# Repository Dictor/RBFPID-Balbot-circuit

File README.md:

# circuit of RBF-PID Balancing Robot 
- [schemetic](./circuit.pdf)
- [pcb](./pcb.pdf)
- [STM32 configuration](./stm32ioc.pdf)

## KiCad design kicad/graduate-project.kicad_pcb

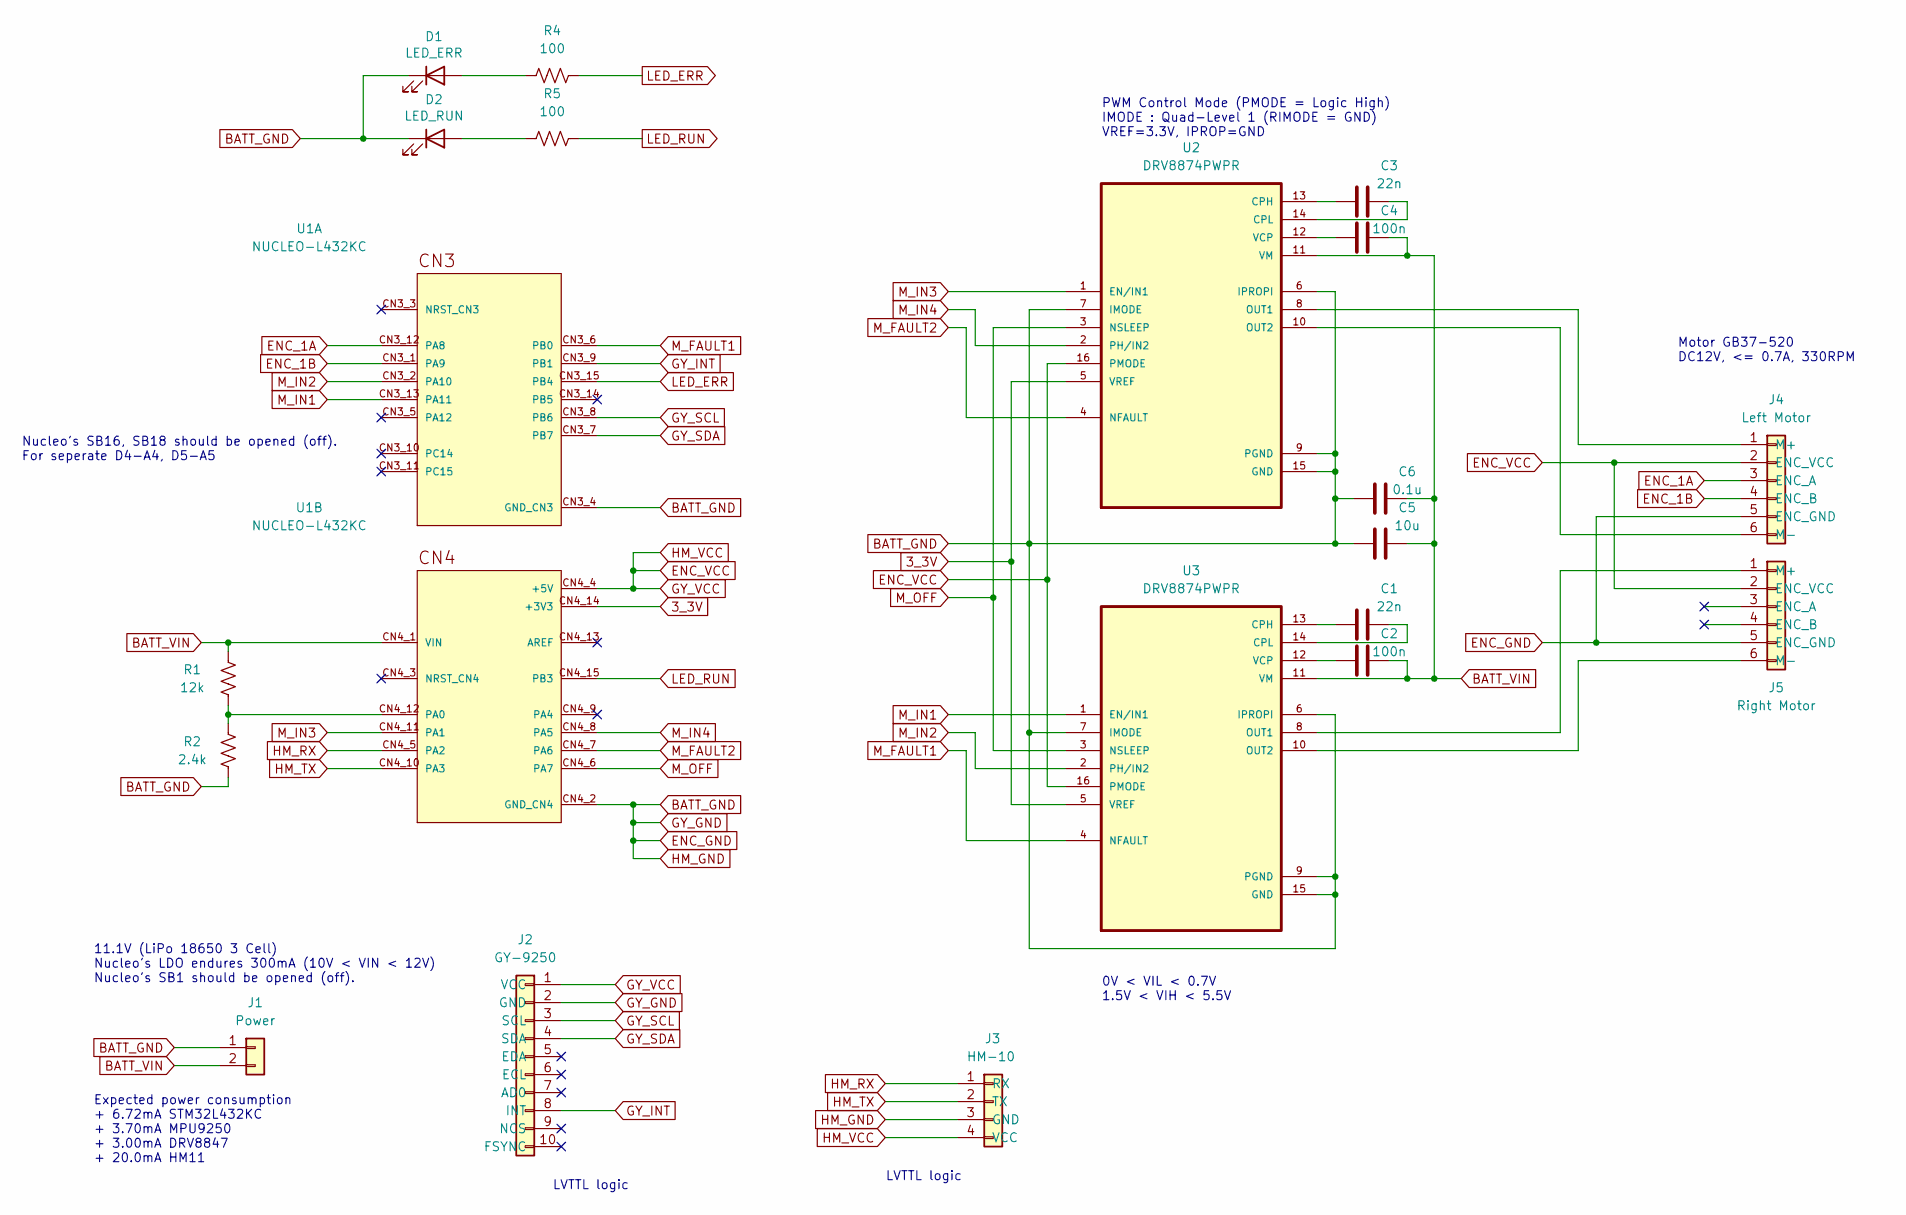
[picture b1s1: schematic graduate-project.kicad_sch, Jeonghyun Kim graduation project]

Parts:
C1, C3: 22n; C_0603_1608Metric
C2, C4: 100n; C_0603_1608Metric
C5: 10u; C_0603_1608Metric
C6: 0.1u; C_0603_1608Metric
D1: LED_ERR; LED_D3.0mm
D2: LED_RUN; LED_D3.0mm
J1: Power; AMASS_XT30U-F_1x02_P5.0mm_Vertical
J2: GY-9250; PinSocket_1x10_P2.54mm_Vertical
J3: HM-10; PinSocket_1x04_P2.54mm_Vertical
J4: Left Motor; PinSocket_1x06_P2.54mm_Vertical
J5: Right Motor; PinSocket_1x06_P2.54mm_Vertical
R1: 12k; R_0603_1608Metric
R2: 2.4k; R_0603_1608Metric
R4, R5: 100; R_0603_1608Metric
U1: NUCLEO-L432KC; MODULE_NUCLEO-L432KC; PARTREV N/A
U2, U3: DRV8874PWPR; SOP65P640X120-17N

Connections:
3_3V: U1.CN4_14 (+3V3), U2.5 (VREF), U3.5 (VREF)
BATT_GND: C5.1, C6.1, D1.1 (K), D2.1 (K), J1.1, J2.2 (GND), J3.3 (GND), J4.5 (ENC_GND), J5.5 (ENC_GND), R2.1, U1.CN3_4 (GND_CN3), U1.CN4_2 (GND_CN4), U2.6 (IPROPI), U2.7 (IMODE), U2.9 (PGND), U2.15 (GND), U2.17, U3.6 (IPROPI), U3.7 (IMODE), U3.9 (PGND), U3.15 (GND), U3.17
BATT_VIN: C2.2, C4.2, C5.2, C6.2, J1.2, R1.2, U1.CN4_1 (VIN), U2.11 (VM), U3.11 (VM)
ENC_1A: J4.3 (ENC_A), U1.CN3_12 (PA8)
ENC_1B: J4.4 (ENC_B), U1.CN3_1 (PA9)
ENC_VCC: J2.1 (VCC), J3.4 (VCC), J4.2 (ENC_VCC), J5.2 (ENC_VCC), U1.CN4_4 (+5V), U2.16 (PMODE), U3.16 (PMODE)
GY_INT: J2.8 (INT), U1.CN3_9 (PB1)
GY_SCL: J2.3 (SCL), U1.CN3_8 (PB6)
GY_SDA: J2.4 (SDA), U1.CN3_7 (PB7)
HM_RX: J3.1 (RX), U1.CN4_5 (PA2)
HM_TX: J3.2 (TX), U1.CN4_10 (PA3)
LED_ERR: R4.2, U1.CN3_15 (PB4)
LED_RUN: R5.2, U1.CN4_15 (PB3)
M_FAULT1: U1.CN3_6 (PB0), U3.4 (NFAULT)
M_FAULT2: U1.CN4_7 (PA6), U2.4 (NFAULT)
M_IN1: U1.CN3_13 (PA11), U3.1 (EN/IN1)
M_IN2: U1.CN3_2 (PA10), U3.2 (PH/IN2)
M_IN3: U1.CN4_11 (PA1), U2.1 (EN/IN1)
M_IN4: U1.CN4_8 (PA5), U2.2 (PH/IN2)
M_OFF: U1.CN4_6 (PA7), U2.3 (NSLEEP), U3.3 (NSLEEP)
unnamed: C1.1, U3.13 (CPH)
unnamed: C1.2, U3.14 (CPL)
unnamed: C2.1, U3.12 (VCP)
unnamed: C3.1, U2.13 (CPH)
unnamed: C3.2, U2.14 (CPL)
unnamed: C4.1, U2.12 (VCP)
unnamed: D1.2 (A), R4.1
unnamed: D2.2 (A), R5.1
unnamed: J5.1 (M+), U3.8 (OUT1)
unnamed: J5.6 (M-), U3.10 (OUT2)
unnamed: R1.1, R2.2, U1.CN4_12 (PA0)
unnamed: J4.1 (M+), U2.8 (OUT1)
unnamed: J4.6 (M-), U2.10 (OUT2)

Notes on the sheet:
11.1V (LiPo 18650 3 Cell) Nucleo's LDO endures 300mA (10V < VIN < 12V) Nucleo's SB1 should be opened (off).
PWM Control Mode (PMODE = Logic High) IMODE : Quad-Level 1 (RIMODE = GND) VREF=3.3V, IPROP=GND
LVTTL logic
Motor GB37-520 DC12V, <= 0.7A, 330RPM
Expected power consumption + 6.72mA STM32L432KC + 3.70mA MPU9250 + 3.00mA DRV8847 + 20.0mA HM11
0V < VIL < 0.7V 1.5V < VIH < 5.5V
Nucleo's SB16, SB18 should be opened (off). For seperate D4-A4, D5-A5

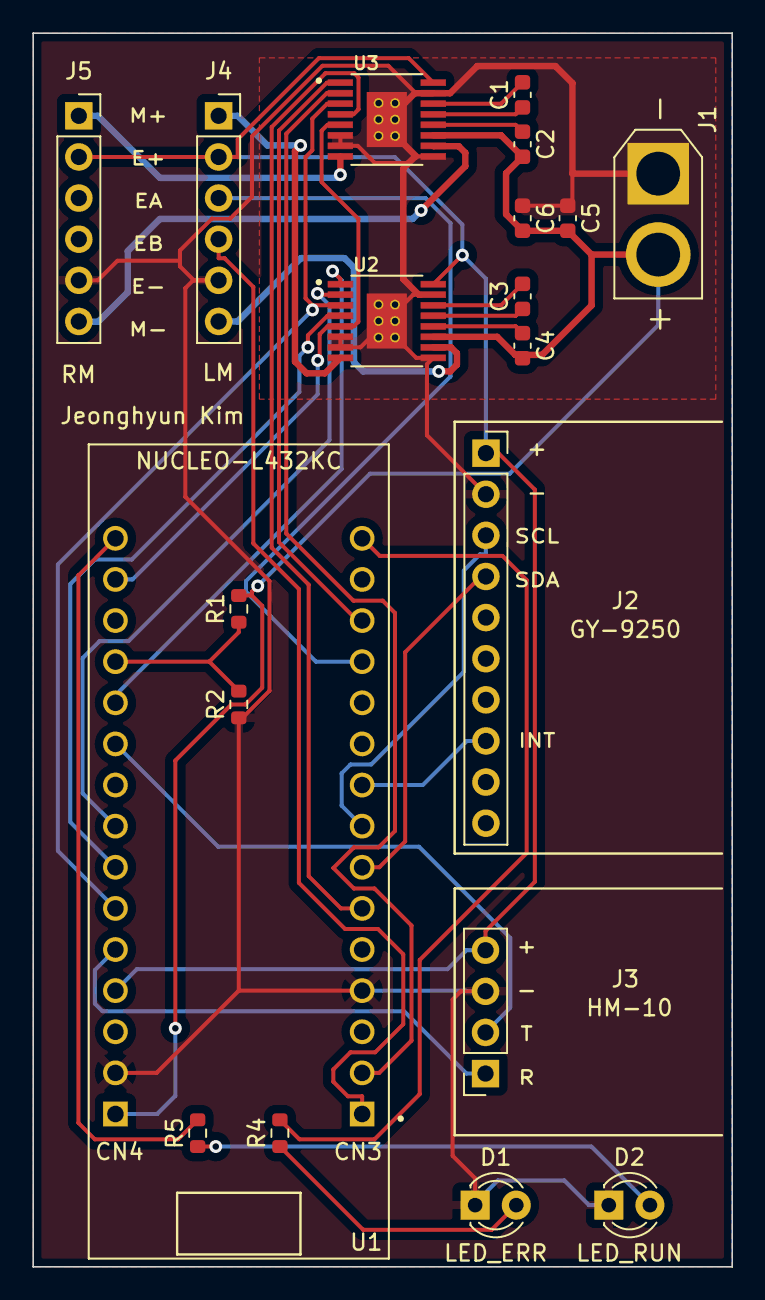
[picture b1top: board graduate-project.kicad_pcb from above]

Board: 2 copper layers, 43.2 x 76.2 mm, 20 parts (0 on the bottom side), 33 nets.

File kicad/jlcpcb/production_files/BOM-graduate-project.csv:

Comment,Designator,Footprint,LCSC
100n,"C2,C4",C_0603_1608Metric,C1591
DRV8874PWPR,"U2,U3",SOP65P640X120-17N,C1855818
22n,"C1,C3",C_0603_1608Metric,C21122
100,"R4,R5",R_0603_1608Metric,C22775
12k,R1,R_0603_1608Metric,C22790
2.4k,R2,R_0603_1608Metric,C465465
10u,C5,C_0603_1608Metric,C70225
0.1u,C6,C_0603_1608Metric,C710755
Power,J1,AMASS_XT30U-F_1x02_P5.0mm_Vertical,C99101

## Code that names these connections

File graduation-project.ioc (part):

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Mcu.Name=STM32L432K(B-C)Ux
Mcu.Package=UFQFPN32
Mcu.UserName=STM32L432KCUx
PA0.Signal=ADCx_IN5
PA1.GPIOParameters=GPIO_Label
PA1.GPIO_Label=M_IN3
PA1.Signal=S_TIM2_CH2
PA10.GPIOParameters=GPIO_Label
PA10.GPIO_Label=M_IN2
PA10.Signal=S_TIM1_CH3
PA11.GPIOParameters=GPIO_Label
PA11.GPIO_Label=M_IN1
PA11.Signal=S_TIM1_CH4
PA13\ (JTMS-SWDIO).GPIOParameters=GPIO_Label
PA13\ (JTMS-SWDIO).GPIO_Label=SWDIO
PA13\ (JTMS-SWDIO).Mode=Serial_Wire
PA13\ (JTMS-SWDIO).Signal=SYS_JTMS-SWDIO
PA14\ (JTCK-SWCLK).GPIOParameters=GPIO_Label
PA14\ (JTCK-SWCLK).GPIO_Label=SWCLK
PA14\ (JTCK-SWCLK).Mode=Serial_Wire
PA14\ (JTCK-SWCLK).Signal=SYS_JTCK-SWCLK
PA2.GPIOParameters=GPIO_Label
PA2.GPIO_Label=VCP_TX
PA2.Mode=Asynchronous
PA2.Signal=USART2_TX
PA3.GPIOParameters=GPIO_Label
PA3.GPIO_Label=VCP_RX
PA3.Mode=Asynchronous
PA3.Signal=USART2_RX
PA5.GPIOParameters=GPIO_Label
PA5.GPIO_Label=M_IN4
PA5.Signal=S_TIM2_CH1
PA6.GPIOParameters=GPIO_Label
PA6.GPIO_Label=M_FAULT2
PA6.Signal=GPXTI6
PA7.GPIOParameters=GPIO_Label
PA7.GPIO_Label=M_OFF
PA7.Signal=GPIO_Output
PA8.GPIOParameters=GPIO_Label
PA8.GPIO_Label=ENC_1A
PA8.Signal=S_TIM1_CH1
PA9.GPIOParameters=GPIO_Label
PA9.GPIO_Label=ENC_1B
PA9.Signal=S_TIM1_CH2
PB0.GPIOParameters=GPIO_Label
PB0.GPIO_Label=M_FAULT
PB0.Signal=GPXTI0
PB1.GPIOParameters=GPIO_Label
PB1.GPIO_Label=GY_INT
PB1.Signal=GPXTI1
PB3\ (JTDO-TRACESWO).GPIOParameters=GPIO_Label
PB3\ (JTDO-TRACESWO).GPIO_Label=LD3 LED_RUN
PB3\ (JTDO-TRACESWO).Signal=GPIO_Output
PB4\ (NJTRST).GPIOParameters=GPIO_Label
PB4\ (NJTRST).GPIO_Label=LED_ERR
PB4\ (NJTRST).Signal=GPIO_Output
PB6.GPIOParameters=GPIO_Label
PB6.GPIO_Label=GY_SCL
PB6.Mode=I2C
PB6.Signal=I2C1_SCL
PB7.GPIOParameters=GPIO_Label
PB7.GPIO_Label=GY_SDA
PB7.Mode=I2C
PB7.Signal=I2C1_SDA
PC14-OSC32_IN\ (PC14).Mode=LSE-External-Oscillator
PC14-OSC32_IN\ (PC14).Signal=RCC_OSC32_IN
PC15-OSC32_OUT\ (PC15).Mode=LSE-External-Oscillator
PC15-OSC32_OUT\ (PC15).Signal=RCC_OSC32_OUT
RCC.HSE_VALUE=8000000
RCC.SYSCLKFreq_VALUE=32000000
RCC.SYSCLKSource=RCC_SYSCLKSOURCE_PLLCLK
board=NUCLEO-L432KC
boardIOC=true

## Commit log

2023-07-31 initial upload
2023-08-18 Change DRV8824 interface mode from 2-Pin to 4-Pin
    * MOD: Drop ENC_2A, B (use only left motor encoder)
2023-11-09 Update pdf plots
